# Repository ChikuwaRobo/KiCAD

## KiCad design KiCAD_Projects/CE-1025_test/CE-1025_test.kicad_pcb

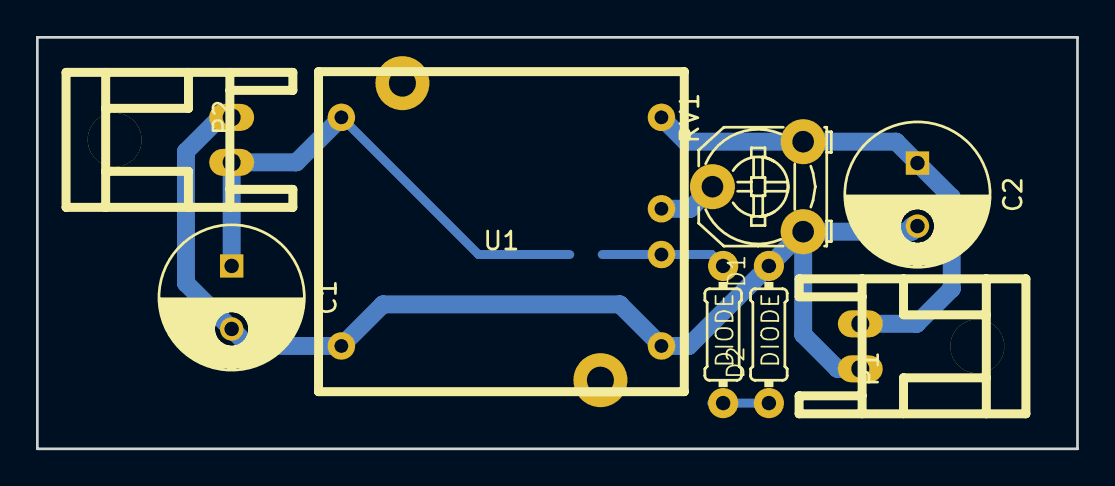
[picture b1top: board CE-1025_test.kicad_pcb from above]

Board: 2 copper layers, 57.8 x 22.9 mm, 9 parts (1 on the bottom side), 6 nets.

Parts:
C1, C2: C; C_Radial_D8_L11.5_P3.5
D1, D2: DIODE; 0204_2f7
P1, P2: CONN_01X02; XA_2LC
R1: R; C1608_WP
RV1: POT; Potentiometer_Triwood_RM-065
U1: TDK_CE-1025

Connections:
+5V: C2.1, P1.2, RV1.3, U1.6
+24V: C1.1, P2.2, R1.1, U1.1
GND: C1.2, C2.2, D2.2, P1.1, P2.1, RV1.1, U1.2, U1.3
unnamed: D1.1, R1.2, U1.4
unnamed: D1.2, D2.1
unnamed: RV1.2, U1.5

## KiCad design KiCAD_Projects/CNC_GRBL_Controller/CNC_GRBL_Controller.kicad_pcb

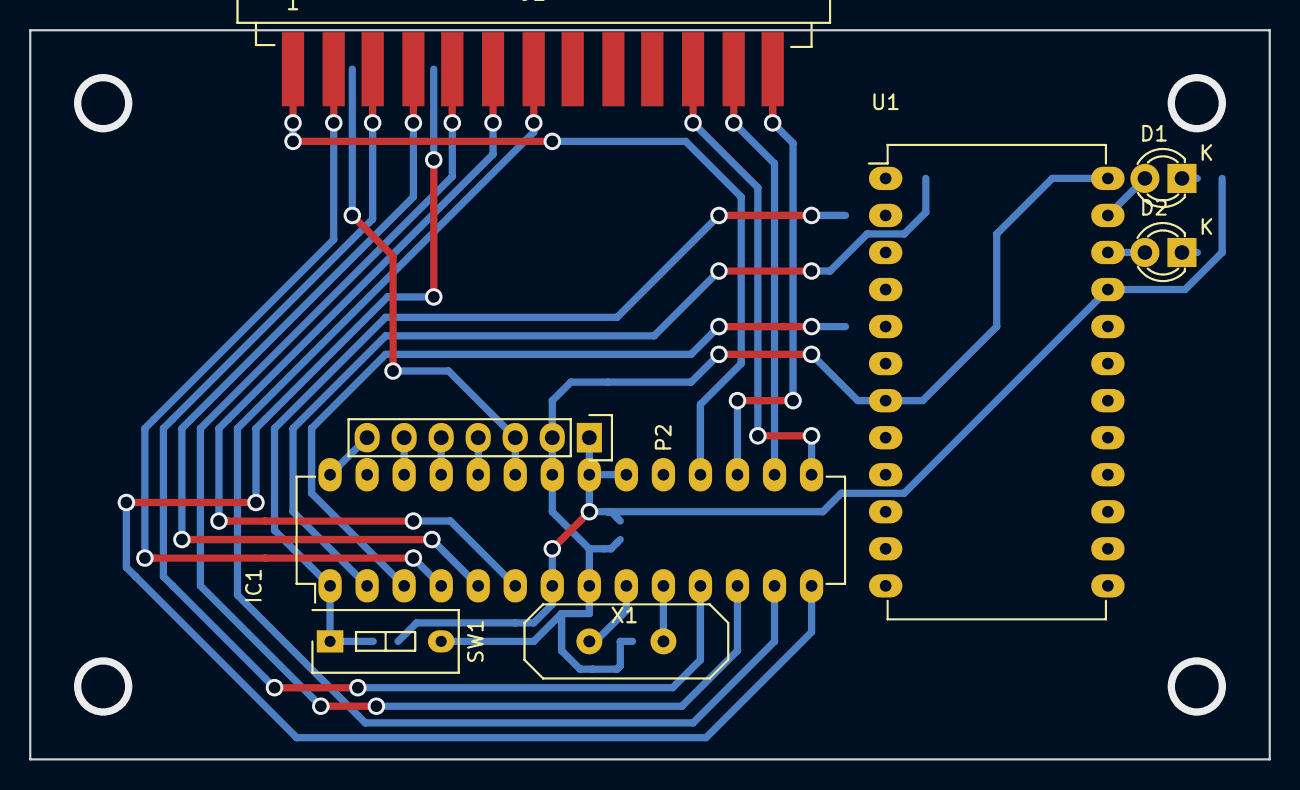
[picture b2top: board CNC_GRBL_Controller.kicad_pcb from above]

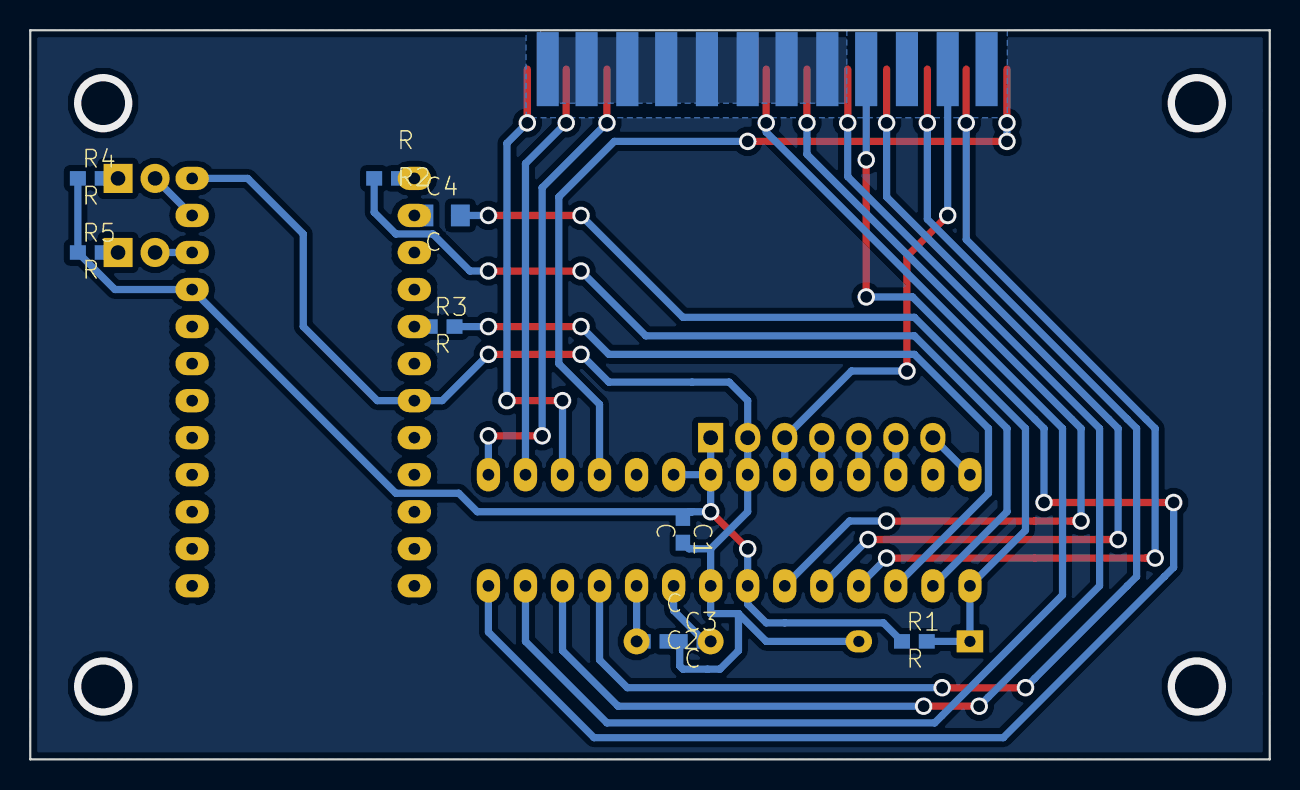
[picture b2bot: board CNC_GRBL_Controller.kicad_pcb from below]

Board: 2 copper layers, 85.0 x 50.0 mm, 17 parts (9 on the bottom side), 30 nets.

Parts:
C1, C2, C3: C; C1608
C4: C; C2012
D1, D2: LED; LED-3MM
IC1: ATMEGA328-P; DIP-28_W7.62mm_LongPads
J1: DB25; DB25F_CI
P2: CONN_01X07; Pin_Header_Straight_1x07
R1, R2, R3, R4, R5: R; C1608
SW1: SW_PUSH_SMALL; SW_DIP_x1_Slide
U1: AE-UM232R; DIP-24_W15.24mm_LongPads
X1: CRYSTAL; HC-18UV

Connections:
+5V: C1.1, IC1.7, IC1.20, IC1.21, P2.1, R1.1, R4.1, R5.1, U1.21
/Arduino_RESET: C4.2, IC1.1, R1.2, SW1.1
/Arduino_RX: IC1.2, R2.2
/Arduino_TX: IC1.3, R3.2
/Coolant_EN: IC1.26, P2.6
/Cycle_Stat: IC1.25, P2.5
/Feed_Hold: IC1.24, P2.4
/Limit_X: IC1.15, J1.11
/Limit_Y: IC1.16, J1.12
/Limit_Z: IC1.17, J1.13
/Probe: IC1.28, P2.7
/Reset/Abort: IC1.23, J1.15, P2.3
/Spindle_EN: IC1.18, J1.1
/Stepper_~EN: IC1.14, J1.17
/X_Dir: IC1.11, J1.3
/X_Step: IC1.4, J1.2
/Y_Dir: IC1.12, J1.5
/Y_Step: IC1.5, J1.4
/Z_Dir: IC1.13, J1.7
/Z_Step: IC1.6, J1.6
GND: C1.2, C2.1, C3.1, IC1.8, IC1.22, J1.18, J1.19, J1.20, J1.21, J1.22, J1.23, J1.24, J1.25, P2.2, SW1.2, U1.7, U1.24
unnamed: C2.2, IC1.10, X1.2
unnamed: C3.2, IC1.9, X1.1
unnamed: C4.1, U1.2
unnamed: D1.1, R4.2
unnamed: D1.2, U1.23
unnamed: D2.1, R5.2
unnamed: D2.2, U1.22
unnamed: R2.1, U1.1
unnamed: R3.1, U1.5

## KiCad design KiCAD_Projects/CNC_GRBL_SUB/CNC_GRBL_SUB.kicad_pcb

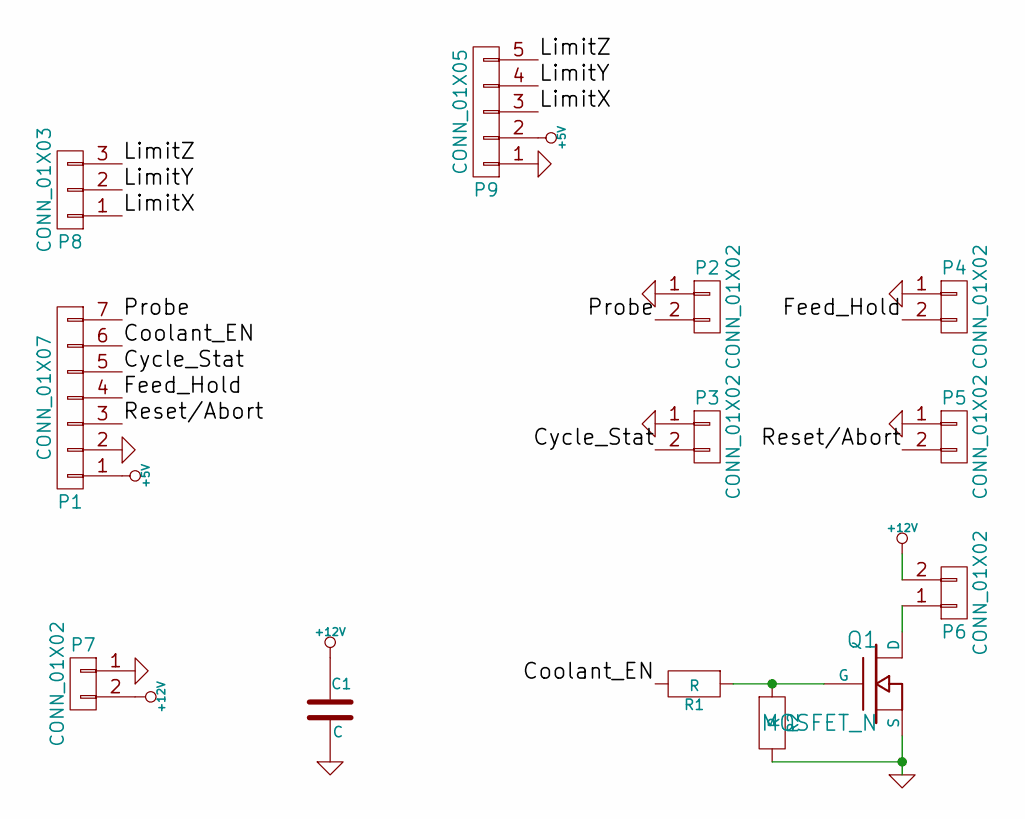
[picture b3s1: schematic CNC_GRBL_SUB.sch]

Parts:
C1: C; C_Radial_D8_L11.5_P3.5
P1: CONN_01X07; Pin_Header_Straight_1x07
P2, P3, P4, P5, P6, P7: CONN_01X02; XA_2LC
P8: CONN_01X03; Pin_Header_Straight_1x03
P9: CONN_01X05; Pin_Header_Angled_1x05
Q1: MOSFET_N; TO-220_Neutral123_Vertical
R1, R2: R; C1608

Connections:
+5V: P1.1, P9.2
+12V: C1.1, P6.2, P7.2
/Coolant_EN: P1.6, R1.2
/Cycle_Stat: P1.5, P3.2
/Feed_Hold: P1.4, P4.2
/LimitX: P8.1, P9.3
/LimitY: P8.2, P9.4
/LimitZ: P8.3, P9.5
/Probe: P1.7, P2.2
/Reset/Abort: P1.3, P5.2
GND: C1.2, P1.2, P2.1, P3.1, P4.1, P5.1, P7.1, P9.1, Q1.S, R2.2
unnamed: P6.1, Q1.D
unnamed: Q1.G, R1.1, R2.1

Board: 2 copper layers, 13 parts (2 on the bottom side), 13 nets, no tracks yet.

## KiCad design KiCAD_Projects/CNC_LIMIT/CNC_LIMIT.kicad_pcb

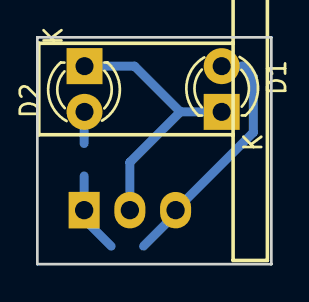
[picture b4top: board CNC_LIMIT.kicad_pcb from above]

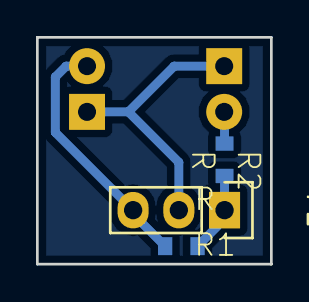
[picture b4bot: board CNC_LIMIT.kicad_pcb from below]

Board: 2 copper layers, 13.0 x 12.6 mm, 5 parts (3 on the bottom side), 4 nets.

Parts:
D1, D2: LED; LED-3MM
P1: CONN_01X03; Pin_Header_Straight_1x03
R1, R2: R; C1608_WP

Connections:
+5V: D1.1, D2.1, P1.2
/OUT: D1.2, P1.3, R1.2
GND: P1.1, R1.1, R2.2
unnamed: D2.2, R2.1

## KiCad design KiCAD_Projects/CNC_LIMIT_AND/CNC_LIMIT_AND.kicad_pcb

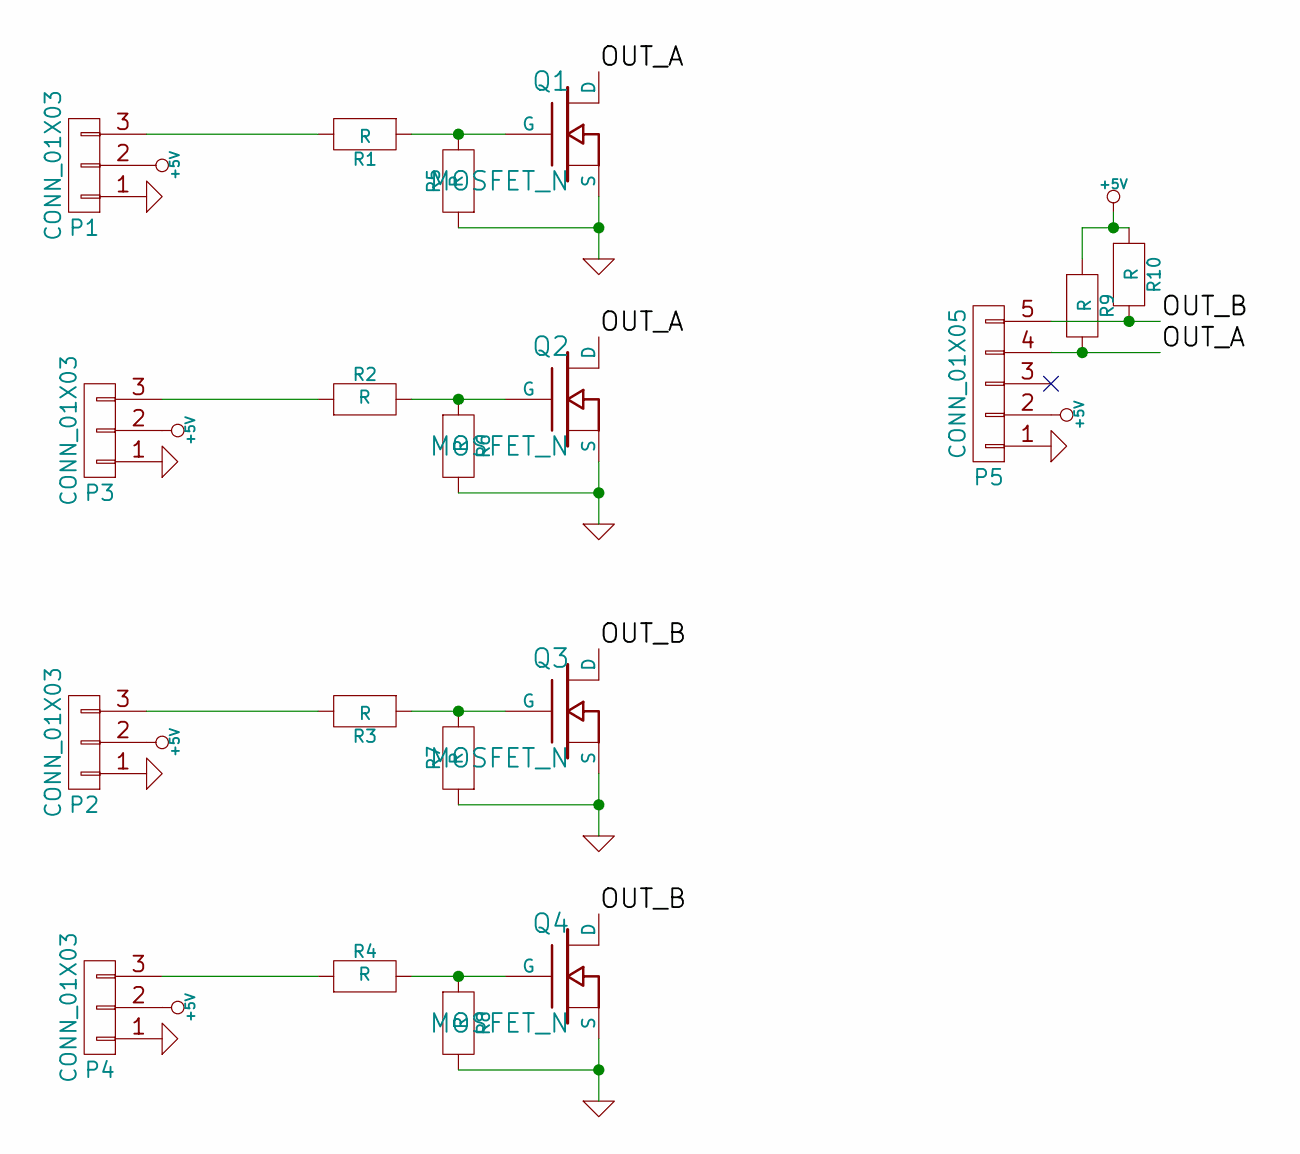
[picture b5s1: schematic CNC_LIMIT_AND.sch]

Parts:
P1, P2, P3, P4: CONN_01X03
P5: CONN_01X05
Q1, Q2, Q3, Q4: MOSFET_N
R1, R2, R3, R4, R5, R6, R7, R8, R9, R10: R

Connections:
+5V: P1.2, P2.2, P3.2, P4.2, P5.2, R9.1, R10.1
/OUT_A: P5.4, Q1.D, Q2.D, R9.2
/OUT_B: P5.5, Q3.D, Q4.D, R10.2
GND: P1.1, P2.1, P3.1, P4.1, P5.1, Q1.S, Q2.S, Q3.S, Q4.S, R5.1, R6.2, R7.1, R8.2
unnamed: P1.3, R1.2
unnamed: P2.3, R3.2
unnamed: P3.3, R2.1
unnamed: P4.3, R4.1
unnamed: Q1.G, R1.1, R5.2
unnamed: Q2.G, R2.2, R6.1
unnamed: Q3.G, R3.1, R7.2
unnamed: Q4.G, R4.2, R8.1

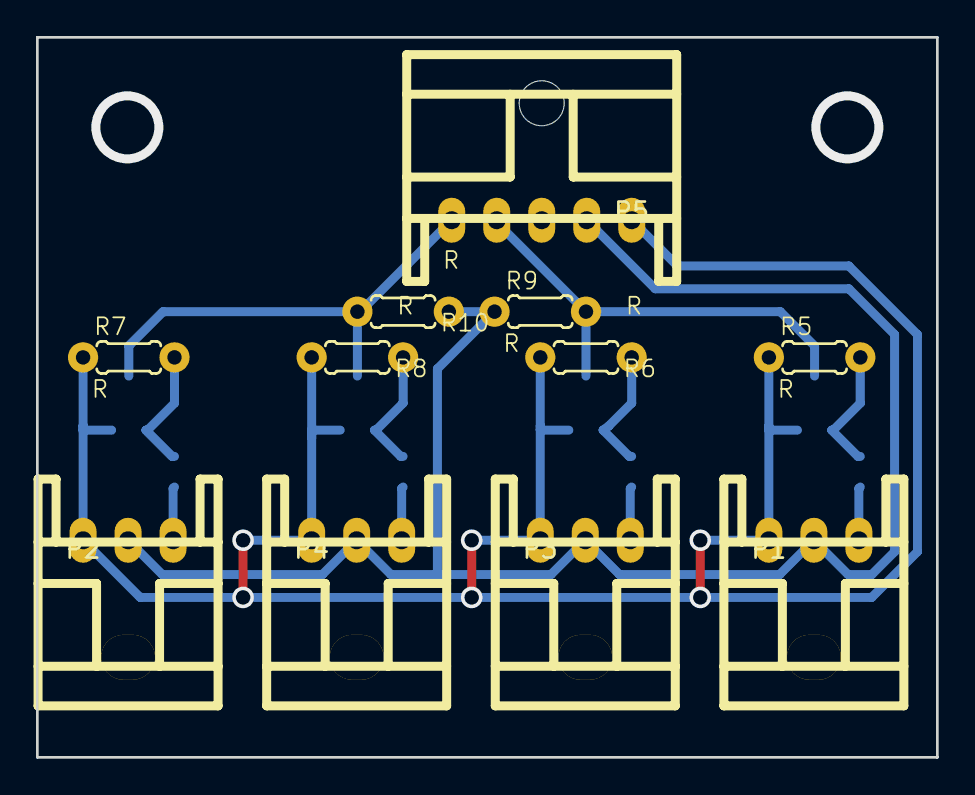
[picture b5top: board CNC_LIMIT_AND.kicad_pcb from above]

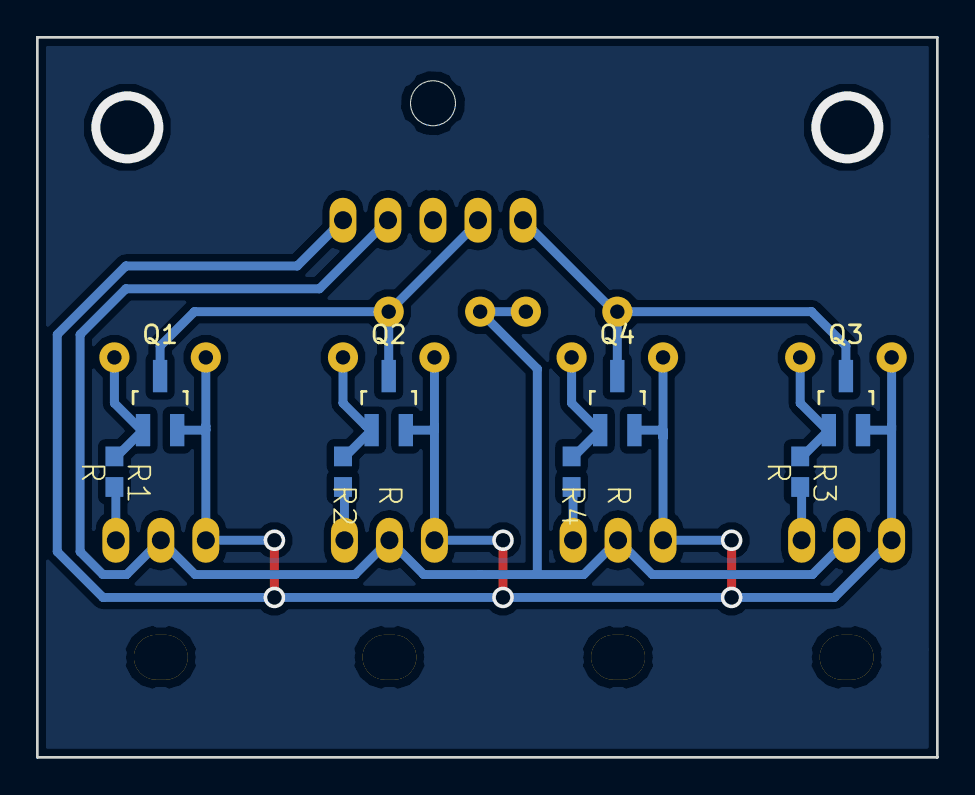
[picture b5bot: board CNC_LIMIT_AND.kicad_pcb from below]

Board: 2 copper layers, 50.0 x 40.0 mm, 19 parts (8 on the bottom side), 12 nets.

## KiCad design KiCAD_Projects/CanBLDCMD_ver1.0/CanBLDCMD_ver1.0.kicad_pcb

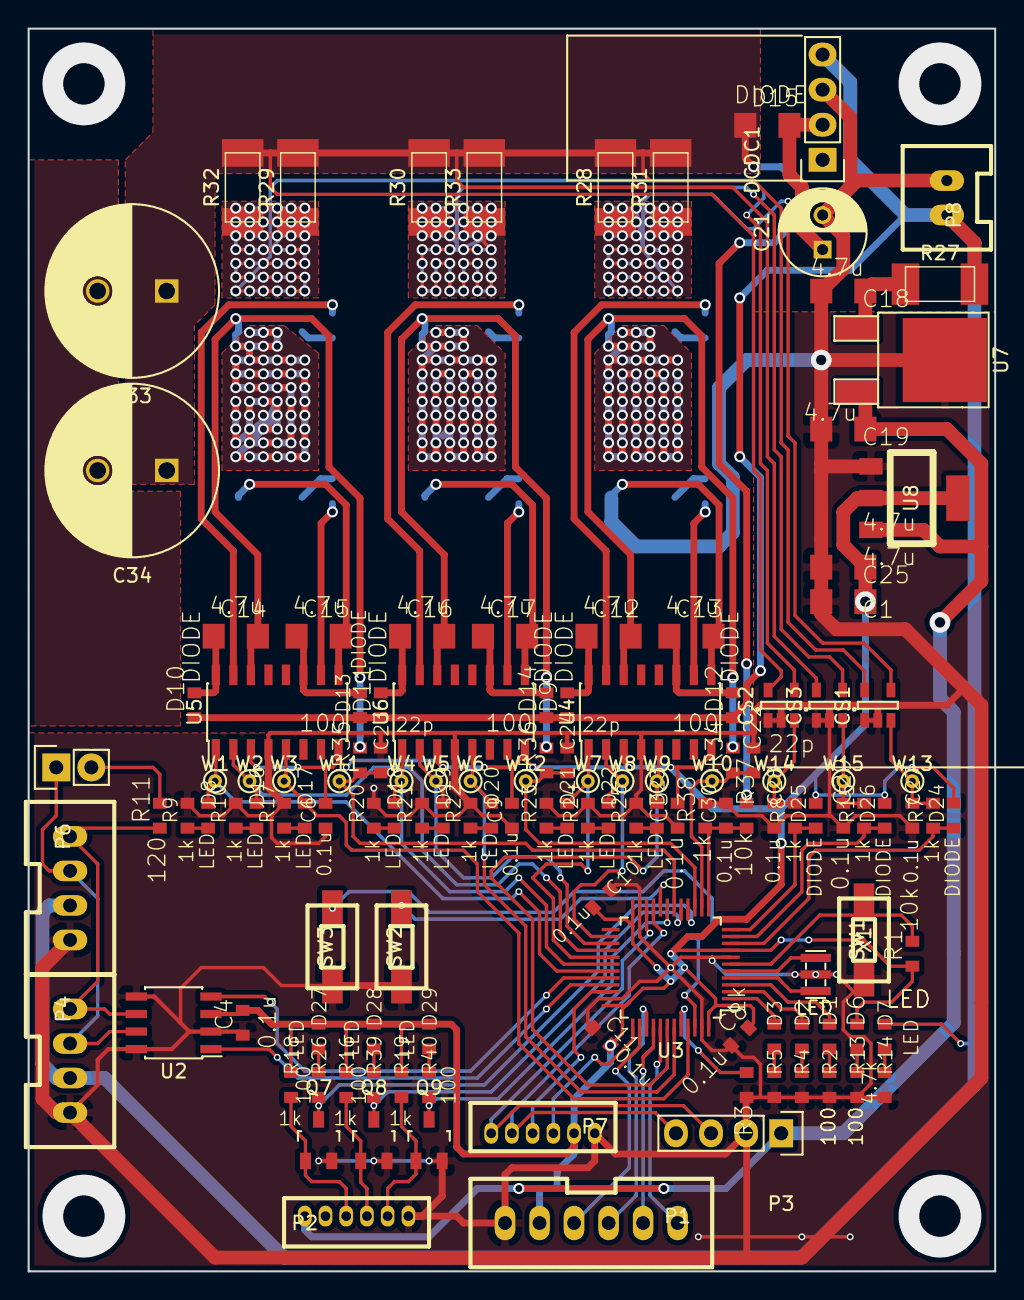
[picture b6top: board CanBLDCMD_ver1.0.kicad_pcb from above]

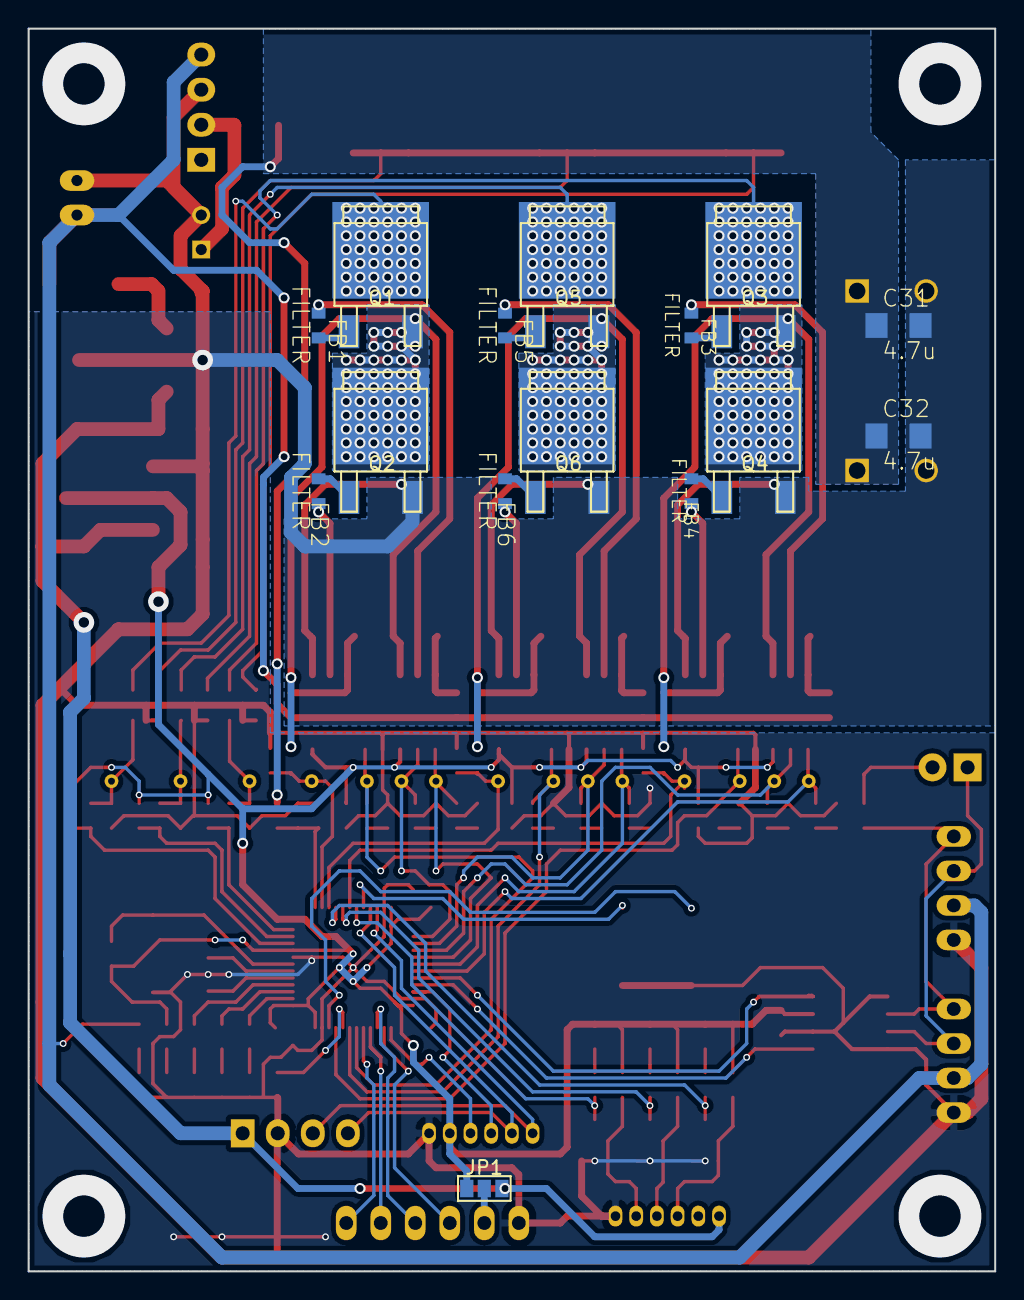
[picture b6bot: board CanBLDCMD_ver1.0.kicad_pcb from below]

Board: 2 copper layers, 70.0 x 90.0 mm, 148 parts (15 on the bottom side), 96 nets.

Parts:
C1, C12, C13, C14, C15, C16, C17, C18, C19, C25, C31, C32: 4.7u; C3216
C3, C4, C6, C8, C9, C10, C11, C27, C28, C29, C30: 0.1u; C1608_WP
C21: 100u; C_Radial_D6.3_L11.2_P2.5
C22, C23, C24: 22p; C1608_WP
C33, C34: 470u; C_Radial_D12.5_L25_P5
CS1, CS2, CS3: TS1102; SOT-23-5
D1, D2, D3, D6, D7, D8, D16, D17, D18, D19, D20, D21, D22, D23, D27, D28, D29: LED; C1608_WP
D9, D10, D11, D12, D13, D14, D24, D25, D26: DIODE; C1608_WP
D15: DIODE; C3216
DCDC1: ChinaDC-DC
FB1, FB2, FB3, FB4, FB5, FB6: FILTER; C1608_WP
JP1: JUMPER3; GS3
P1: CONN_01X06; XA_6T
P2, P7: CONN_01X06; ZH_6T
P3: CONN_01X04; Socket_Strip_Straight_1x04
P4, P6: CONN_01X04; XA_4T
P5: CONN_01X02; Pin_Header_Straight_1x02
P8: CONN_01X02; XA_2T
Q1, Q2, Q3, Q4, Q5, Q6: MOSFET_N; SOT-428_GDS_compact
Q7, Q8, Q9: MOSFET_N; SOT-23_Handsoldering
R1, R37: 10k; C1608_WP
R2, R4, R5, R13, R26, R34, R35, R36, R39, R40: 100; C1608_WP
R3, R7, R8, R9, R10, R15, R16, R17, R18, R19, R20, R21, R22, R23, R24, R25, R38: 1k; C1608_WP
R11: 120; C1608_WP
R14: 4.7k; C1608_WP
R27: 10; R5025
R28, R29, R30, R31, R32, R33: 1m; R5025
SW1, SW2, SW3: SW_PUSH; RP_SMD_Button
U2: MAX3051; SOIC-8_3.9x4.9mm_Pitch1.27mm
U3: STM32F103_48; LQFP-48_7x7mm_Pitch0.5mm
U4, U5, U6: SI8275; SOIC-16_3.9x9.9mm_Pitch1.27mm
U7: 7805; TO-252-2Lead_regu
U8: NCP1117ST33T3G; SOT-223_reg
W1, W2, W3, W4, W5, W6, W7, W8, W9, W10, W11, W12, W13, W14, W15: TEST_1P; PINTST
X1: ceralock; Resonator_3×1.3mm

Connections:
+3.3V: C1.1, C3.2, C4.2, C6.2, C8.2, C9.2, C10.2, C11.2, C25.1, D6.1, D24.2, D25.2, D26.2, D27.1, D28.1, D29.1, JP1.1, P7.2, R1.1, R16.1, R18.1, R19.1, U2.3, U3.1, U3.9, U3.24, U3.36, U3.48, U4.3, U4.8, U5.3, U5.8, U6.3, U6.8, U8.2
+5V: C19.1, JP1.3, P2.1, P3.1, U7.VO, U8.3
+12V: D7.1, D9.1, D10.1, D11.1, D12.1, D13.1, D14.1, DCDC1.4, P4.2, P6.2, P8.2, R27.2
+BATT: C31.1, C32.1, C33.1, C34.1, CS1.5, CS2.5, CS3.5, D15.1, R28.2, R29.2, R30.2, R31.2, R32.2, R33.2, R37.1
/BOOT0: R3.2, U3.44
/BattSense: C30.1, R37.2, R38.1, U3.13
/CANH: P4.3, P5.1, P6.3, U2.7
/CANL: P4.4, P6.4, R11.1, U2.6
/CAN_RX: U2.4, U3.32
/CAN_TX: U2.1, U3.33
/CS_U: D25.1, R8.1, U3.12
/CS_V: D26.1, R15.1, U3.11
/CS_W: D24.1, R7.1, U3.10
/EN_U: D17.1, U3.45, U5.5, W3.1
/EN_V: D20.1, U3.43, U6.5, W6.1
/EN_W: D23.1, U3.42, U4.5, W9.1
/HALL_0: Q7.D, R26.2, U3.16
/HALL_1: Q8.D, R39.2, U3.17
/HALL_2: Q9.D, R40.2, U3.19
/LED_C: D3.1, U3.2
/LED_D: D2.1, U3.3
/LED_E: D1.1, U3.4
/NRST: R1.2, SW1.2, U3.7
/OSC_IN: U3.5, X1.3
/OSC_OUT: U3.6, X1.1
/OUT_U: C14.2, Q3.S, Q4.D, R35.2, U5.14
/OUT_V: C16.2, Q5.S, Q6.D, R36.2, U6.14
/OUT_W: C12.2, Q1.S, Q2.D, R34.2, U4.14
/PWM_U_H: D8.1, U3.31, U5.1, W1.1
/PWM_U_L: D16.1, U3.28, U5.2, W2.1
/PWM_V_H: D18.1, U3.30, U6.1, W4.1
/PWM_V_L: D19.1, U3.27, U6.2, W5.1
/PWM_W_H: D21.1, U3.29, U4.1, W7.1
/PWM_W_L: D22.1, U3.26, U4.2, W8.1
/SPI_MISO: P1.5, U3.40
/SPI_MOSI: P1.6, U3.41
/SPI_NSS: P1.3, U3.38
/SPI_SCK: P1.4, U3.39
/SW1: SW2.2, U3.20
/SW2: SW3.2, U3.46
/SWCLK: P7.3, U3.37
/SWDIO: P7.4, U3.34
/USART_RX: P3.3, P7.6, U3.22
/USART_TX: P3.4, P7.5, U3.21
/Vsense_U: C23.2, R35.1, U3.18, W11.1
/Vsense_V: C24.2, R36.1, U3.15, W12.1
/Vsense_W: C22.2, R34.1, U3.14, W10.1
GND: C1.2, C3.1, C4.1, C6.1, C8.1, C9.1, C10.1, C11.1, C13.2, C15.2, C17.2, C18.2, C19.2, C21.2, C22.1, C23.1, C24.1, C25.2, C27.2, C28.2, C29.2, C30.2, C31.2, C32.2, C33.2, C34.2, CS1.1, CS1.2, CS2.1, CS2.2, CS3.1, CS3.2, DCDC1.3, P1.1, P2.6, P3.2, P4.1, P6.1, P7.1, P8.1, Q2.S, Q4.S, Q6.S, Q7.S, Q8.S, Q9.S, R2.2, R3.1, R4.2, R5.2, R9.2, R10.2, R13.2, R14.2, R17.2, R20.2, R21.2, R22.2, R23.2, R24.2, R25.2, R38.2, SW1.1, SW2.1, SW3.1, U2.2, U2.5, U2.8, U3.8, U3.23, U3.35, U3.47, U4.4, U4.9, U5.4, U5.9, U6.4, U6.9, U7.GND, U8.1, X1.2
unnamed: C12.1, D9.2, U4.16
unnamed: C13.1, D12.2, U4.11
unnamed: C14.1, D10.2, U5.16
unnamed: C15.1, D13.2, U5.11
unnamed: C16.1, D11.2, U6.16
unnamed: C17.1, D14.2, U6.11
unnamed: C18.1, R27.1, U7.VI
unnamed: C21.1, D15.2, DCDC1.2
unnamed: C27.1, CS1.3, R7.2, W13.1
unnamed: C28.1, CS2.3, R8.2, W14.1
unnamed: C29.1, CS3.3, R15.2, W15.1
unnamed: CS1.4, Q1.D, R28.1, R31.1
unnamed: CS2.4, Q3.D, R29.1, R32.1
unnamed: CS3.4, Q5.D, R30.1, R33.1
unnamed: D1.2, R2.1
unnamed: D2.2, R4.1
unnamed: D3.2, R5.1
unnamed: D6.2, R13.1
unnamed: D7.2, R14.1
unnamed: D8.2, R9.1
unnamed: D16.2, R10.1
unnamed: D17.2, R17.1
unnamed: D18.2, R20.1
unnamed: D19.2, R21.1
unnamed: D20.2, R22.1
unnamed: D21.2, R23.1
unnamed: D22.2, R24.1
unnamed: D23.2, R25.1
unnamed: D27.2, R26.1
unnamed: D28.2, R39.1
unnamed: D29.2, R40.1
unnamed: FB1.1, U4.15
unnamed: FB1.2, Q1.G
unnamed: FB2.1, U4.10
unnamed: FB2.2, Q2.G
unnamed: FB3.1, U5.15
unnamed: FB3.2, Q3.G
unnamed: FB4.1, U5.10
unnamed: FB4.2, Q4.G
unnamed: FB5.1, U6.15
unnamed: FB5.2, Q5.G
unnamed: FB6.1, U6.10
unnamed: FB6.2, Q6.G
unnamed: JP1.2, P1.2
unnamed: P2.3, Q7.G, R18.2
unnamed: P2.4, Q8.G, R16.2
unnamed: P2.5, Q9.G, R19.2
unnamed: P5.2, R11.2
